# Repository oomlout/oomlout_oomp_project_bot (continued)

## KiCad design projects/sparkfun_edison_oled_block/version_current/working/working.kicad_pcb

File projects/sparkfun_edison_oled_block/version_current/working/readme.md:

# Edison_OLED_Block by sparkfun  
This is a harvested standardized copy of a project from github.  
The original project can be found at:  
https://github.com/sparkfun/Edison_OLED_Block  
Please consult that link for additional, details, files, and license information.  
Note: It was auto harvested and if the original repo had more than one board file or anything out of the ordinary the files here are likely not representative.

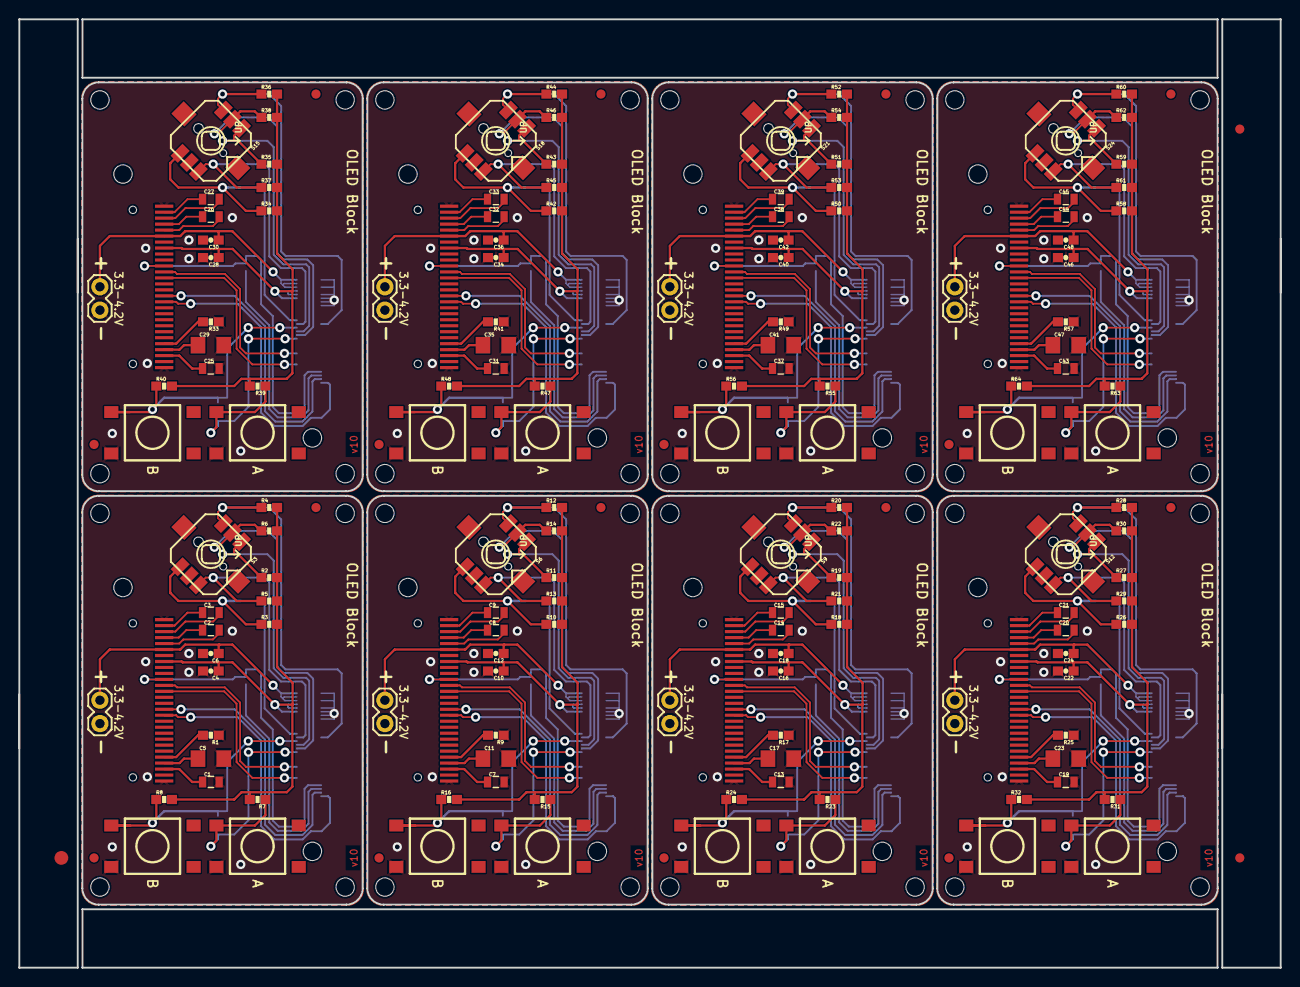
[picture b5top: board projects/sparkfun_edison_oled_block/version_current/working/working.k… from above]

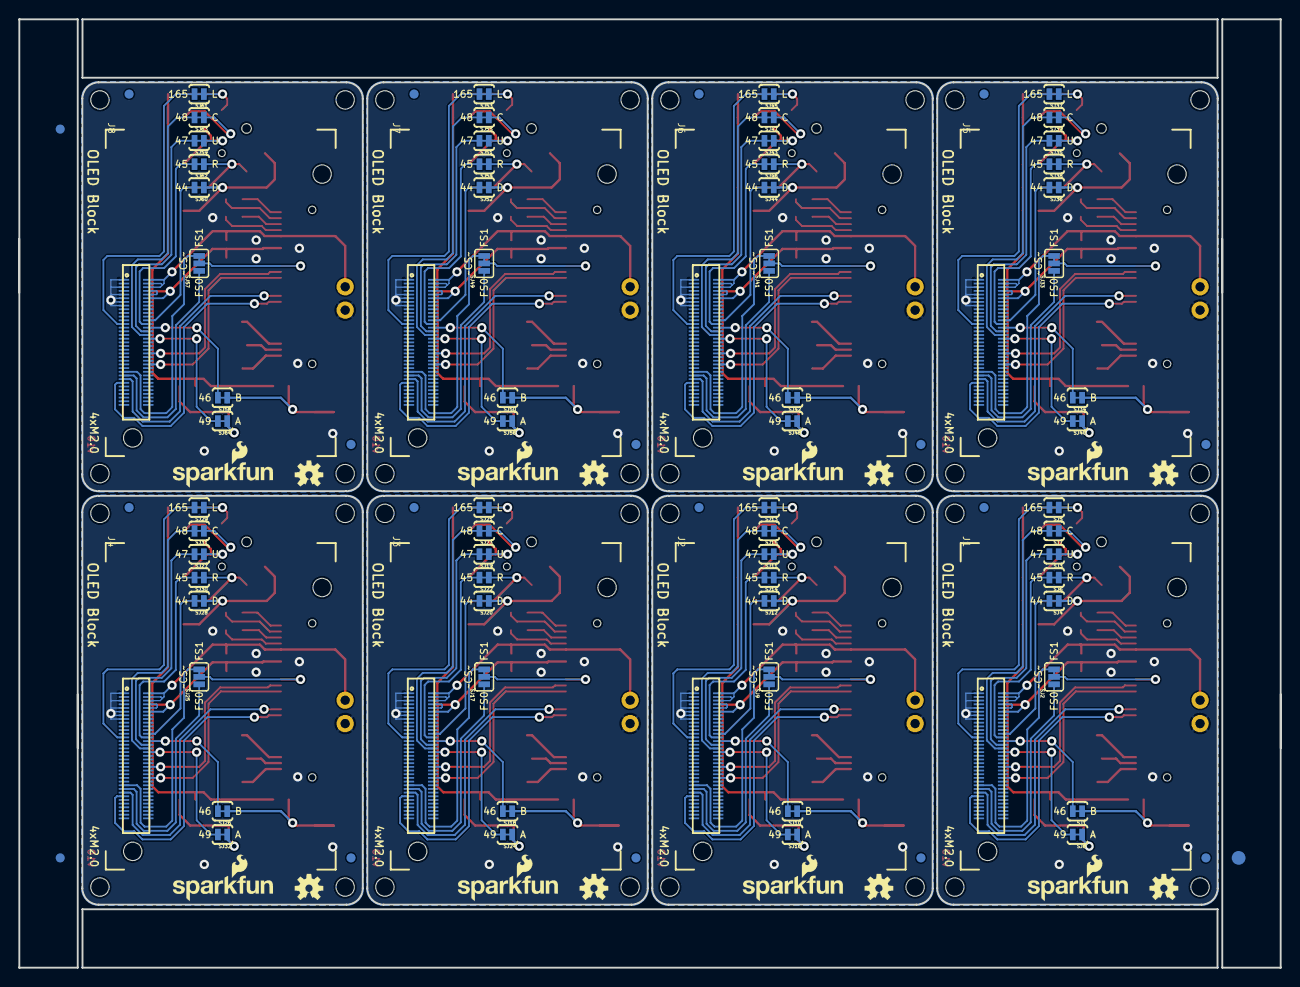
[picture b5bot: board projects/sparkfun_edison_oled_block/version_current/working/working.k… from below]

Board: 4 copper layers, 137.2 x 103.1 mm, 310 parts (107 on the bottom side), 256 nets.

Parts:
@HOLE0, @HOLE1, @HOLE2, @HOLE3, @HOLE4, @HOLE5, @HOLE6, @HOLE7, @HOLE8, @HOLE9, @HOLE10, @HOLE11, @HOLE12, @HOLE13, @HOLE14, @HOLE15, @HOLE16, @HOLE17, @HOLE18, @HOLE19, @HOLE20, @HOLE21, @HOLE22, @HOLE23, @HOLE24, @HOLE25, @HOLE26, @HOLE27, @HOLE28, @HOLE29, @HOLE30, @HOLE31: (no value)
C1, C7, C13, C19, C25, C31, C37, C43: 2.2uF; 0805
C2, C3, C8, C9, C14, C15, C20, C21, C26, C27, C32, C33, C38, C39, C44, C45: 1uF X5R; 0805
C4, C6, C10, C12, C16, C18, C22, C24, C28, C30, C34, C36, C40, C42, C46, C48: 1uF; 0603-CAP
C5, C11, C17, C23, C29, C35, C41, C47: 4.7uF/16V; 1206
E$1, E$2: FIDUCIAL-1.5X3
E$3, E$4, E$5, E$6: FIDUCIAL-1X2
FID1, FID2, FID3, FID4, FID5, FID6, FID7, FID8, FID9, FID10, FID11, FID12, FID13, FID14, FID15, FID16, FID17, FID18, FID19, FID20, FID21, FID22, FID23, FID24, FID25, FID26, FID27, FID28, FID29, FID30, FID31, FID32: FIDUCIAL1X2; FIDUCIAL-1X2
J1, J2, J3, J4, J5, J6, J7, J8: EDISON_CONNECTOR_FULLMOUNTING_HOLES; EDISON_DAUGHTER
JP1, JP2, JP3, JP4, JP5, JP6, JP7, JP8: M02PTH; 1X02
LOGO1, LOGO2, LOGO5, LOGO7, LOGO9, LOGO11, LOGO13, LOGO15: OSHW-LOGOS; OSHW-LOGO-S
LOGO3, LOGO4, LOGO6, LOGO8, LOGO10, LOGO12, LOGO14, LOGO16: SFE_LOGO_NAME_FLAME.1_INCH; SFE_LOGO_NAME_FLAME_.1
OLED1, OLED2, OLED3, OLED4, OLED5, OLED6, OLED7, OLED8: OLED0.66; OLED-0.66-64X48
R1, R9, R17, R25, R33, R41, R49, R57: 390k; 0603-RES
R2, R3, R4, R5, R6, R7, R8, R10, R11, R12, R13, R14, R15, R16, R18, R19, R20, R21, R22, R23, R24, R26, R27, R28, R29, R30, R31, R32, R34, R35, R36, R37, R38, R39, R40, R42, R43, R44, R45, R46, R47, R48, R50, R51, R52, R53, R54, R55, R56, R58, R59, R60, R61, R62, R63, R64: 10K; 0603-RES
S1, S4, S7, S10, S13, S16, S19, S22: Button A; TACTILE_SWITCH_TALL
S2, S5, S8, S11, S14, S17, S20, S23: Button B; TACTILE_SWITCH_TALL
S3, S6, S9, S12, S15, S18, S21, S24: JOYSTICK_MINI
SJ1, SJ3, SJ4, SJ5, SJ6, SJ7, SJ8, SJ10, SJ11, SJ12, SJ13, SJ14, SJ15, SJ16, SJ18, SJ19, SJ20, SJ21, SJ22, SJ23, SJ24, SJ26, SJ27, SJ28, SJ29, SJ30, SJ31, SJ32, SJ34, SJ35, SJ36, SJ37, SJ38, SJ39, SJ40, SJ42, SJ43, SJ44, SJ45, SJ46, SJ47, SJ48, SJ50, SJ51, SJ52, SJ53, SJ54, SJ55, SJ56, SJ58, SJ59, SJ60, SJ61, SJ62, SJ63, SJ64: PAD-JUMPER-2-NC_BY_TRACE_YES_SILK
SJ2, SJ9, SJ17, SJ25, SJ33, SJ41, SJ49, SJ57: CS_SEL; PAD-JUMPER-3-2OF3_NC_BY_TRACE_YES_SILK_FULL_BOX

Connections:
1.8V: C4.1, J1.12, OLED1.8, R2.2, R3.2, R4.2, R5.2, R6.2, R7.2, R8.2
1.8V1: C10.1, J2.12, OLED2.8, R10.2, R11.2, R12.2, R13.2, R14.2, R15.2, R16.2
1.8V2: C16.1, J3.12, OLED3.8, R18.2, R19.2, R20.2, R21.2, R22.2, R23.2, R24.2
1.8V3: C22.1, J4.12, OLED4.8, R26.2, R27.2, R28.2, R29.2, R30.2, R31.2, R32.2
1.8V4: C28.1, J5.12, OLED5.8, R34.2, R35.2, R36.2, R37.2, R38.2, R39.2, R40.2
1.8V5: C34.1, J6.12, OLED6.8, R42.2, R43.2, R44.2, R45.2, R46.2, R47.2, R48.2
1.8V6: C40.1, J7.12, OLED7.8, R50.2, R51.2, R52.2, R53.2, R54.2, R55.2, R56.2
1.8V7: C46.1, J8.12, OLED8.8, R58.2, R59.2, R60.2, R61.2, R62.2, R63.2, R64.2
3.3V: J1.8, J1.10
3.3V1: J2.8, J2.10
3.3V2: J3.8, J3.10
3.3V3: J4.8, J4.10
3.3V4: J5.8, J5.10
3.3V5: J6.8, J6.10
3.3V6: J7.8, J7.10
3.3V7: J8.8, J8.10
BUT_A: R7.1, S1.A2, SJ8.1
BUT_A1: R15.1, S4.A2, SJ16.1
BUT_A2: R23.1, S7.A2, SJ24.1
BUT_A3: R31.1, S10.A2, SJ32.1
BUT_A4: R39.1, S13.A2, SJ40.1
BUT_A5: R47.1, S16.A2, SJ48.1
BUT_A6: R55.1, S19.A2, SJ56.1
BUT_A7: R63.1, S22.A2, SJ64.1
BUT_B: R8.1, S2.A2, SJ1.1
BUT_B1: R16.1, S5.A2, SJ10.1
BUT_B2: R24.1, S8.A2, SJ18.1
BUT_B3: R32.1, S11.A2, SJ26.1
BUT_B4: R40.1, S14.A2, SJ34.1
BUT_B5: R48.1, S17.A2, SJ42.1
BUT_B6: R56.1, S20.A2, SJ50.1
BUT_B7: R64.1, S23.A2, SJ58.1
C1N: C2.2, OLED1.5
C1N1: C8.2, OLED2.5
C1N2: C14.2, OLED3.5
C1N3: C20.2, OLED4.5
C1N4: C26.2, OLED5.5
C1N5: C32.2, OLED6.5
C1N6: C38.2, OLED7.5
C1N7: C44.2, OLED8.5
C1P: C2.1, OLED1.4
C1P1: C8.1, OLED2.4
C1P2: C14.1, OLED3.4
C1P3: C20.1, OLED4.4
C1P4: C26.1, OLED5.4
C1P5: C32.1, OLED6.4
C1P6: C38.1, OLED7.4
C1P7: C44.1, OLED8.4
C2N: C3.2, OLED1.3
C2N1: C9.2, OLED2.3
C2N2: C15.2, OLED3.3
C2N3: C21.2, OLED4.3
C2N4: C27.2, OLED5.3
C2N5: C33.2, OLED6.3
C2N6: C39.2, OLED7.3
C2N7: C45.2, OLED8.3
C2P: C3.1, OLED1.2
C2P1: C9.1, OLED2.2
C2P2: C15.1, OLED3.2
C2P3: C21.1, OLED4.2
C2P4: C27.1, OLED5.2
C2P5: C33.1, OLED6.2
C2P6: C39.1, OLED7.2
C2P7: C45.1, OLED8.2
GND: C1.2, C4.2, C5.2, C6.2, J1.1, J1.5, J1.9, J1.11, J1.13, J1.15, JP1.1, OLED1.1, OLED1.7, OLED1.9, OLED1.10, OLED1.27, OLED1.28, R1.1, S1.B2, S2.B2, S3.GND
GND1: C7.2, C10.2, C11.2, C12.2, J2.1, J2.5, J2.9, J2.11, J2.13, J2.15, JP2.1, OLED2.1, OLED2.7, OLED2.9, OLED2.10, OLED2.27, OLED2.28, R9.1, S4.B2, S5.B2, S6.GND
GND2: C13.2, C16.2, C17.2, C18.2, J3.1, J3.5, J3.9, J3.11, J3.13, J3.15, JP3.1, OLED3.1, OLED3.7, OLED3.9, OLED3.10, OLED3.27, OLED3.28, R17.1, S7.B2, S8.B2, S9.GND
GND3: C19.2, C22.2, C23.2, C24.2, J4.1, J4.5, J4.9, J4.11, J4.13, J4.15, JP4.1, OLED4.1, OLED4.7, OLED4.9, OLED4.10, OLED4.27, OLED4.28, R25.1, S10.B2, S11.B2, S12.GND
GND4: C25.2, C28.2, C29.2, C30.2, J5.1, J5.5, J5.9, J5.11, J5.13, J5.15, JP5.1, OLED5.1, OLED5.7, OLED5.9, OLED5.10, OLED5.27, OLED5.28, R33.1, S13.B2, S14.B2, S15.GND
GND5: C31.2, C34.2, C35.2, C36.2, J6.1, J6.5, J6.9, J6.11, J6.13, J6.15, JP6.1, OLED6.1, OLED6.7, OLED6.9, OLED6.10, OLED6.27, OLED6.28, R41.1, S16.B2, S17.B2, S18.GND
GND6: C37.2, C40.2, C41.2, C42.2, J7.1, J7.5, J7.9, J7.11, J7.13, J7.15, JP7.1, OLED7.1, OLED7.7, OLED7.9, OLED7.10, OLED7.27, OLED7.28, R49.1, S19.B2, S20.B2, S21.GND
GND7: C43.2, C46.2, C47.2, C48.2, J8.1, J8.5, J8.9, J8.11, J8.13, J8.15, JP8.1, OLED8.1, OLED8.7, OLED8.9, OLED8.10, OLED8.27, OLED8.28, R57.1, S22.B2, S23.B2, S24.GND
GP1: J2.48, OLED2.13
GP2: J2.42, OLED2.12
GP3: J2.34, SJ16.2
GP4: J2.32, SJ15.2
GP5: J2.30, SJ11.2
GP6: J2.28, SJ10.2
GP7: J2.26, SJ14.2
GP8: J2.25, SJ13.2
GP9: J2.24, SJ12.2
GP10: J3.48, OLED3.13
GP11: J3.42, OLED3.12
GP12: J3.34, SJ24.2
GP13: J3.32, SJ23.2
GP14: J1.48, OLED1.13
GP15: J1.42, OLED1.12
GP16: J3.30, SJ19.2
GP17: J3.28, SJ18.2
GP18: J3.26, SJ22.2
GP19: J3.25, SJ21.2
GP20: J3.24, SJ20.2
GP21: J4.48, OLED4.13
GP22: J4.42, OLED4.12
GP23: J4.34, SJ32.2
GP24: J4.32, SJ31.2
GP25: J4.30, SJ27.2
GP26: J4.28, SJ26.2
GP27: J4.26, SJ30.2
GP28: J4.25, SJ29.2
GP29: J4.24, SJ28.2
GP30: J5.48, OLED5.13
GP31: J5.42, OLED5.12
GP32: J5.34, SJ40.2
GP33: J5.32, SJ39.2
GP34: J5.30, SJ35.2
GP35: J5.28, SJ34.2
GP36: J5.26, SJ38.2
GP37: J5.25, SJ37.2
GP38: J5.24, SJ36.2
GP39: J6.48, OLED6.13
GP40: J6.42, OLED6.12
GP41: J6.34, SJ48.2
GP42: J6.32, SJ47.2
GP43: J6.30, SJ43.2
GP44: J1.24, SJ4.2
GP45: J1.26, SJ6.2
GP46: J1.28, SJ1.2
GP47: J1.30, SJ3.2
GP48: J1.32, SJ7.2
GP49: J1.34, SJ8.2
GP50: J6.28, SJ42.2
GP51: J6.26, SJ46.2
GP52: J6.25, SJ45.2
GP53: J6.24, SJ44.2
GP54: J7.48, OLED7.13
GP55: J7.42, OLED7.12
GP56: J7.34, SJ56.2
GP57: J7.32, SJ55.2
GP58: J7.30, SJ51.2
GP59: J7.28, SJ50.2
GP60: J7.26, SJ54.2
GP61: J7.25, SJ53.2
GP62: J7.24, SJ52.2
GP63: J8.48, OLED8.13
GP64: J8.42, OLED8.12
GP65: J8.34, SJ64.2
GP66: J8.32, SJ63.2
GP67: J8.30, SJ59.2
GP68: J8.28, SJ58.2
GP69: J8.26, SJ62.2
GP70: J8.25, SJ61.2
GP71: J8.24, SJ60.2
GP109_SPI_2_CLK: J1.55, OLED1.16
GP109_SPI_2_CLK1: J2.55, OLED2.16
GP109_SPI_2_CLK2: J3.55, OLED3.16
GP109_SPI_2_CLK3: J4.55, OLED4.16
GP109_SPI_2_CLK4: J5.55, OLED5.16
GP109_SPI_2_CLK5: J6.55, OLED6.16
GP109_SPI_2_CLK6: J7.55, OLED7.16
GP109_SPI_2_CLK7: J8.55, OLED8.16
GP110_SPI_2_FS0: J1.53, SJ2.1
GP110_SPI_2_FS1: J2.53, SJ9.1
GP110_SPI_2_FS2: J3.53, SJ17.1
GP110_SPI_2_FS3: J4.53, SJ25.1
GP110_SPI_2_FS4: J5.53, SJ33.1
GP110_SPI_2_FS5: J6.53, SJ41.1
GP110_SPI_2_FS6: J7.53, SJ49.1
GP110_SPI_2_FS7: J8.53, SJ57.1
GP111_SPI_2_FS1: J1.51, SJ2.3
GP111_SPI_2_FS2: J2.51, SJ9.3
GP111_SPI_2_FS3: J3.51, SJ17.3
GP111_SPI_2_FS4: J4.51, SJ25.3
GP111_SPI_2_FS5: J5.51, SJ33.3
GP111_SPI_2_FS6: J6.51, SJ41.3
GP111_SPI_2_FS7: J7.51, SJ49.3
GP111_SPI_2_FS8: J8.51, SJ57.3
GP115_SPI_2_TXD: J1.57, OLED1.17
GP115_SPI_2_TXD1: J2.57, OLED2.17
GP115_SPI_2_TXD2: J3.57, OLED3.17
GP115_SPI_2_TXD3: J4.57, OLED4.17
GP115_SPI_2_TXD4: J5.57, OLED5.17
GP115_SPI_2_TXD5: J6.57, OLED6.17
GP115_SPI_2_TXD6: J7.57, OLED7.17
GP115_SPI_2_TXD7: J8.57, OLED8.17
GP165: J1.25, SJ5.2
IREF: OLED1.24, R1.2
IREF1: OLED2.24, R9.2
IREF2: OLED3.24, R17.2
IREF3: OLED4.24, R25.2
IREF4: OLED5.24, R33.2
IREF5: OLED6.24, R41.2
IREF6: OLED7.24, R49.2
IREF7: OLED8.24, R57.2
JOY_C: R6.1, S3.CTR, SJ7.1
JOY_C1: R14.1, S6.CTR, SJ15.1
JOY_C2: R22.1, S9.CTR, SJ23.1
JOY_C3: R30.1, S12.CTR, SJ31.1
JOY_C4: R38.1, S15.CTR, SJ39.1
JOY_C5: R46.1, S18.CTR, SJ47.1
JOY_C6: R54.1, S21.CTR, SJ55.1
JOY_C7: R62.1, S24.CTR, SJ63.1
JOY_D: R3.1, S3.D, SJ4.1
JOY_D1: R10.1, S6.D, SJ12.1
JOY_D2: R18.1, S9.D, SJ20.1
JOY_D3: R26.1, S12.D, SJ28.1
JOY_D4: R34.1, S15.D, SJ36.1
JOY_D5: R42.1, S18.D, SJ44.1
JOY_D6: R50.1, S21.D, SJ52.1
JOY_D7: R58.1, S24.D, SJ60.1
JOY_L: R4.1, S3.C, SJ5.1
JOY_L1: R12.1, S6.C, SJ13.1
JOY_L2: R20.1, S9.C, SJ21.1
JOY_L3: R28.1, S12.C, SJ29.1
JOY_L4: R36.1, S15.C, SJ37.1
JOY_L5: R44.1, S18.C, SJ45.1
JOY_L6: R52.1, S21.C, SJ53.1
JOY_L7: R60.1, S24.C, SJ61.1
JOY_R: R5.1, S3.B, SJ6.1
JOY_R1: R13.1, S6.B, SJ14.1
JOY_R2: R21.1, S9.B, SJ22.1
JOY_R3: R29.1, S12.B, SJ30.1
JOY_R4: R37.1, S15.B, SJ38.1
JOY_R5: R45.1, S18.B, SJ46.1
JOY_R6: R53.1, S21.B, SJ54.1
JOY_R7: R61.1, S24.B, SJ62.1
JOY_U: R2.1, S3.A, SJ3.1
JOY_U1: R11.1, S6.A, SJ11.1
JOY_U2: R19.1, S9.A, SJ19.1
JOY_U3: R27.1, S12.A, SJ27.1
JOY_U4: R35.1, S15.A, SJ35.1
JOY_U5: R43.1, S18.A, SJ43.1
JOY_U6: R51.1, S21.A, SJ51.1
JOY_U7: R59.1, S24.A, SJ59.1
OLED_~CS: OLED1.11, SJ2.2
OLED_~CS1: OLED2.11, SJ9.2
OLED_~CS2: OLED3.11, SJ17.2
OLED_~CS3: OLED4.11, SJ25.2
OLED_~CS4: OLED5.11, SJ33.2
OLED_~CS5: OLED6.11, SJ41.2
OLED_~CS6: OLED7.11, SJ49.2
OLED_~CS7: OLED8.11, SJ57.2
VCC: C1.1, OLED1.26
VCC1: C7.1, OLED2.26
VCC2: C13.1, OLED3.26
VCC3: C19.1, OLED4.26
VCC4: C25.1, OLED5.26
VCC5: C31.1, OLED6.26
VCC6: C37.1, OLED7.26
VCC7: C43.1, OLED8.26
VCOMH: C5.1, OLED1.25
VCOMH1: C11.1, OLED2.25
VCOMH2: C17.1, OLED3.25
VCOMH3: C23.1, OLED4.25
VCOMH4: C29.1, OLED5.25
VCOMH5: C35.1, OLED6.25
VCOMH6: C41.1, OLED7.25
VCOMH7: C47.1, OLED8.25
VSYS: C6.1, J1.2, J1.4, J1.6, JP1.2, OLED1.6
VSYS1: C12.1, J2.2, J2.4, J2.6, JP2.2, OLED2.6
VSYS2: C18.1, J3.2, J3.4, J3.6, JP3.2, OLED3.6
VSYS3: C24.1, J4.2, J4.4, J4.6, JP4.2, OLED4.6
VSYS4: C30.1, J5.2, J5.4, J5.6, JP5.2, OLED5.6
VSYS5: C36.1, J6.2, J6.4, J6.6, JP6.2, OLED6.6
VSYS6: C42.1, J7.2, J7.4, J7.6, JP7.2, OLED7.6
VSYS7: C48.1, J8.2, J8.4, J8.6, JP8.2, OLED8.6

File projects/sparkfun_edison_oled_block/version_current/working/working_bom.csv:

"Id";"Designator";"Footprint";"Quantity";"Designation";"Supplier and ref";
1;"R45,R11,R4,R52,R47,R28,R29,R59,R31,R15,R27,R26,R62,R61,R58,R21,R48,R23,R22,R14,R6,R53,R60,R55,R38,R7,R37,R8,R56,R19,R35,R24,R40,R30,R20,R18,R16,R64,R43,R36,R12,R50,R39,R44,R46,R5,R34,R32,R13,R3,R2,R54,R63,R10,R42,R51";"0603-RES";56;"10K";;;
2;"JP3,JP2,JP8,JP7,JP4,JP6,JP1,JP5";"1X02";8;"M02PTH";;;
3;"C7,C13,C1,C43,C37,C19,C31,C25";"0805";8;"2.2uF";;;
4;"E$1,E$2";"FIDUCIAL-1.5X3";2;"";;;
5;"OLED3,OLED7,OLED8,OLED2,OLED1,OLED6,OLED5,OLED4";"OLED-0.66-64X48";8;"OLED0.66";;;
6;"C29,C41,C5,C11,C47,C35,C23,C17";"1206";8;"4.7uF/16V";;;
7;"@HOLE27,@HOLE4,@HOLE11,@HOLE10,@HOLE12,@HOLE6,@HOLE9,@HOLE13,@HOLE0,@HOLE21,@HOLE26,@HOLE2,@HOLE5,@HOLE1,@HOLE19,@HOLE3,@HOLE31,@HOLE17,@HOLE30,@HOLE16,@HOLE25,@HOLE24,@HOLE18,@HOLE8,@HOLE20,@HOLE28,@HOLE7,@HOLE14,@HOLE29,@HOLE15,@HOLE22,@HOLE23";"";32;"";;;
8;"FID4,FID26,FID28,FID10,FID2,FID8,FID22,FID24,FID12,FID16,FID14,FID20,FID6,FID30,FID32,FID18,FID11,FID13,FID9,FID23,FID25,FID7,FID15,FID27,FID29,FID19,FID1,FID5,FID31,FID21,FID17,FID3";"FIDUCIAL-1X2";32;"FIDUCIAL1X2";;;
9;"C10,C36,C30,C12,C4,C6,C46,C22,C34,C40,C24,C18,C42,C28,C48,C16";"0603-CAP";16;"1uF";;;
10;"S10,S19,S1,S13,S22,S7,S16,S4";"TACTILE_SWITCH_TALL";8;"Button A";;;
11;"S14,S8,S23,S17,S20,S2,S5,S11";"TACTILE_SWITCH_TALL";8;"Button B";;;
12;"C21,C44,C38,C27,C9,C32,C26,C39,C8,C45,C33,C3,C15,C2,C14,C20";"0805";16;"1uF X5R";;;
13;"R1,R9,R57,R41,R17,R25,R33,R49";"0603-RES";8;"390k";;;
14;"S3,S9,S21,S12,S18,S24,S15,S6";"JOYSTICK_MINI";8;"";;;
15;"E$5,E$4,E$3,E$6";"FIDUCIAL-1X2";4;"";;;
16;"SJ60,SJ36,SJ48,SJ50,SJ8,SJ47,SJ61,SJ26,SJ54,SJ35,SJ56,SJ31,SJ38,SJ52,SJ58,SJ44,SJ4,SJ34,SJ20,SJ24,SJ32,SJ46,SJ23,SJ5,SJ10,SJ64,SJ59,SJ43,SJ13,SJ45,SJ37,SJ63,SJ14,SJ11,SJ22,SJ12,SJ29,SJ51,SJ16,SJ19,SJ40,SJ27,SJ15,SJ30,SJ62,SJ3,SJ53,SJ18,SJ7,SJ42,SJ1,SJ55,SJ21,SJ39,SJ6,SJ28";"PAD-JUMPER-2-NC_BY_TRACE_YES_SILK";56;"";;;
17;"LOGO4,LOGO14,LOGO12,LOGO8,LOGO16,LOGO6,LOGO3,LOGO10";"SFE_LOGO_NAME_FLAME_.1";8;"SFE_LOGO_NAME_FLAME.1_INCH";;;
18;"J5,J7,J3,J6,J8,J4,J1,J2";"EDISON_DAUGHTER";8;"EDISON_CONNECTOR_FULLMOUNTING_HOLES";;;
19;"LOGO2,LOGO11,LOGO15,LOGO13,LOGO5,LOGO7,LOGO9,LOGO1";"OSHW-LOGO-S";8;"OSHW-LOGOS";;;
20;"SJ41,SJ9,SJ17,SJ57,SJ49,SJ2,SJ33,SJ25";"PAD-JUMPER-3-2OF3_NC_BY_TRACE_YES_SILK_FULL_BOX";8;"CS_SEL";;;
